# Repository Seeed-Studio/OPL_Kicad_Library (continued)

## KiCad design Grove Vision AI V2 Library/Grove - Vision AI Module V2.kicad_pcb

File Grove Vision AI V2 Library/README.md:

# Grove Vision AI V2 Library

This is the library for Grove Vision AI V2 and its case.

## Highlights(Content of Tables)

- [**The case for Grove Vision AI V2 - Himax**](#jump7)
- [**Preparatory Work: KiCad Download and Library Download**](#jump1)
- [**How to add and use Seeed OPL Footprint Libraries(Grove Vision AI V2)**](#jump2)
- [**How to add and use Seeed OPL Symbol Libraries(Grove Vision AI V2)**](#jump3)
- [**Scale up Your Creation With Seeed Studio Fusion**](#jump4)
- [**Co-Create with Seeed Studio**](#jump5)
- [**Resoureces**](#jump6)

## <span id="jump7">The case for Grove Vision AI V2 - Himax</span>

You can find the case here as well.

## <span id="jump1">Preparatory Work: KiCad Download and Library Download </span>

1. You can refer to this [link](https://www.kicad.org/download/) to download the KiCad software.

2. You can [download](https://github.com/Seeed-Studio/OPL_Kicad_Library) the "OPL_KiCad_Library" or use command to clone:

```
git clone https://github.com/Seeed-Studio/OPL_Kicad_Library.git
```

## How to add and use Seeed OPL Footprint Libraries

### <span id="jump2"> Take Grove Vision AI V2 and XIAO footprint as an Example </span>

1. Open KiCad and refer to `File -> Open Project`.

2. Find the "Gorve Vision AI V2 Library" and open the project:

3. Double click the "Grove Vision AI V2" PCB file and you will see below:

4. Refer to the `Perferences -> Manage Footprint Libraries`

5. Here is the existed footprint libraries and you can click the button below:

6. Find the "Gorve Vision AI V2 Library" and open the folder that contains the boards footprint:

Now you have added the "XIAO footprint library"

7. You can click here to use the added library:

8. Search for "seeed" and you can check the footprint added:

9. Click "ok" and you can add the XIAO RP2040 footprint into the "Grove Vision VI V2".

10. You can change any component on the Grove Vision VI V2 module and make it your own project.

## <span id="jump3"> How to add and use Seeed OPL Symbol Libraries </span>

### Take Grove Vision AI V2 and Sensor-Transducer as an Example:

1. Open KiCad and refer to `File -> Open Project`.

2. Find the "Gorve Vision AI V2 Library" and open the project:

3. Double click the "Grove Vision AI V2" .sch file and you will see below:

4. Refer to the `Perferences -> Manage Symbol Libraries`

5. Here is the existed symbol libraries and you can click the button below:

6. Find the "OPL_Sensor-Transducer" lib file:

Now you have added the "OPL_Sensor-Transducer library"

7. You can click here to use the added library:

8. Search for "OPL" and you can check the symbol added:

9. Click "ok" and you can add it into the "Grove Vision VI V2".

10. You can change any component on the Grove Vision VI V2 module and make it your own project.

## <span id="jump4"> Scale up Your Creation With Seeed Studio Fusion </span>

Seeed Studio Fusion serves as the comprehensive service platform for Seeed Studio, a global one-stop online platform offering PCB manufacturing, PCB assembly and hardware customization with global sourcing capability. Whether you need prototyping, mass production, custom solutions for open-source products, or the transformation of your creative ideas into profitable products, Seeed Studio Fusion can meet your requirements.

- [PCB/PCBA Design](https://www.seeedstudio.com/fusion_pcb.html)
- [Fusion Website](https://www.seeedstudio.com/fusion.html)
- **Email Contact**: fusion@seeed.io

## <span id="jump5"> Co-Create with Seeed Studio </span>

Leverage our Co-Create Program to transform your advanced prototype into a commercially successful product! This program is designed to optimize your product's journey from prototype to market by handling marketing, packaging, and distribution, allowing you to concentrate on refining your product. Upon acceptance of your prototype by Seeed, it will be showcased on the Seeed Studio marketplace. You'll receive a portion of the profits for each unit sold.

- [Application Form](https://docs.google.com/forms/d/e/1FAIpQLSe3A7_rIbn2OLO4JyJd_poGZodItCaRy6M6-3FtdqL3xG1Usg/viewform)
- [Co-Create Website](https://www.seeedstudio.com/co-create.html)

## <span id="jump6"> Resources </span>

- [Seeed Studio Open Parts List](https://files.seeedstudio.com/wiki/OPL/OPL_list.xlsx)

<!-- ## Even More Components!

As of last December, the [OPL has expanded](http://www.seeedstudio.com/blog/2018/12/04/just-what-you-wanted-for-xmas-introducing-the-new-shenzhen-open-parts-library-with-over-10000-parts/) from 800 components to more than 10,000 with the introduction of the new Shenzhen OPL. The original Seeed OPL is a catalog of components from Seeed’s own inventory, we have the parts and, we have been using them in our own production processes for years. The Shenzhen OPL contains parts from Shenzhen’s biggest components distributor that Seeed can quickly order for turnkey PCBA. While the sources are different, both can be used together with the Seeed Fusion PCBA service and reduce the production time to 7 days.

But with all the new components and many more to come, we don’t have enough resources to create the footprints for all of them. So, we are asking for help from you and the wider community to gradually build-up the library with us. As more and more users utilize the OPL and update the component libraries, the better the library will become for everyone. 

To assist with the process, we have designated a team of engineers to maintain the library and GitHub repositories. They will also help draw some footprints and connect schematic symbols. But while our engineers do their best to check each footprint, with the sheer number of components, it is inevitable that some errors will be present. It is unavoidable. So to make up for it, Seeed Fusion has introduced a re-manufacture promise: If an error in the library requires the boards to be re-manufactured, then we will re-manufacture the corrected boards for you for free. By using this library, you accept this potential risk.

## Footprint Design Guidelines
It is still early days, and we have a lot of catching up to do. So, the most important additions at this stage are unique symbols and footprints and any generic footprints that are missing. Part-specific symbols that use generic footprints and slight variations of generic footprints can be added later.

For consistency and ease of use, we would greatly appreciate it if everyone followed the same guidelines for new additions to the library:

-	The previous component libraries have been re-organized to match the Shenzhen OPL’s categorization. Please add new entries to the relevant sub-library according to the online OPL library’s classification.
-	Please take the time to study [KiCad’s own Library Convention](http://kicad-pcb.org/libraries/klc/) and ensure that the new footprints comply. Please refer to other footprints in the OPL or KiCad’s built-in footprints for reference. 
-	For MPN specific footprints, please follow the existing footprint naming convention for the footprint and name the corresponding schematic symbol with the manufacturer part number.

### Notes:
- #### The current version of the KiCad Library has been completely revamped in response to all the feedback we have recieved. Originally a direct import of the Eagle library, the old library did not comply with KiCad guidelines and placed features on the wrong layers. For the latest version, we have throroughly investigated the issues and revised (nearly) all of the footprints. Let us know if you think we missed something!

-	The Seeed OPL component libraries have been updated to match the Shenzhen OPL categories to aid in merging the two libraries. Some components will have moved to new homes, but this has not been updated on the website OPL library yet. We will update this soon!
-	Some of the original Seeed OPL KiCad component footprints have not been updated to match KiCad’s design guidelines yet. They are safe to use, and the pads are correct, but they may look a little ugly.
-	Unlike previous versions, we have uploaded the files individually as opposed to a whole zip file. We hope this will help you follow standard GitHub workflow to contribute changes. (Thanks for your feedback!)

There is a lot to consider in managing a large library like this, so we would greatly appreciate any ideas and feedback regarding how we can make the library more user-friendly. We’ll be monitoring the discussion section and the designated OPL section in our forums. You are also welcome to let us know by [e-mail](mailto:fusion@seeed.cc).

We hope the new maintained library will prove to be an invaluable resource to all of our PCBA users and beyond.

## Resources
1. A KiCad Bill-of-Materials (BOM) plugin to follow SeeedStudio's Fusion PCBA assembly service's template, This plugin is set up to use the KiCad schematic's part data as it is provided in Seeed Studio's Open Parts Library (OPL) collection for KiCad. - https://github.com/imrehg/kicad-bom-seeedstudio

 -->

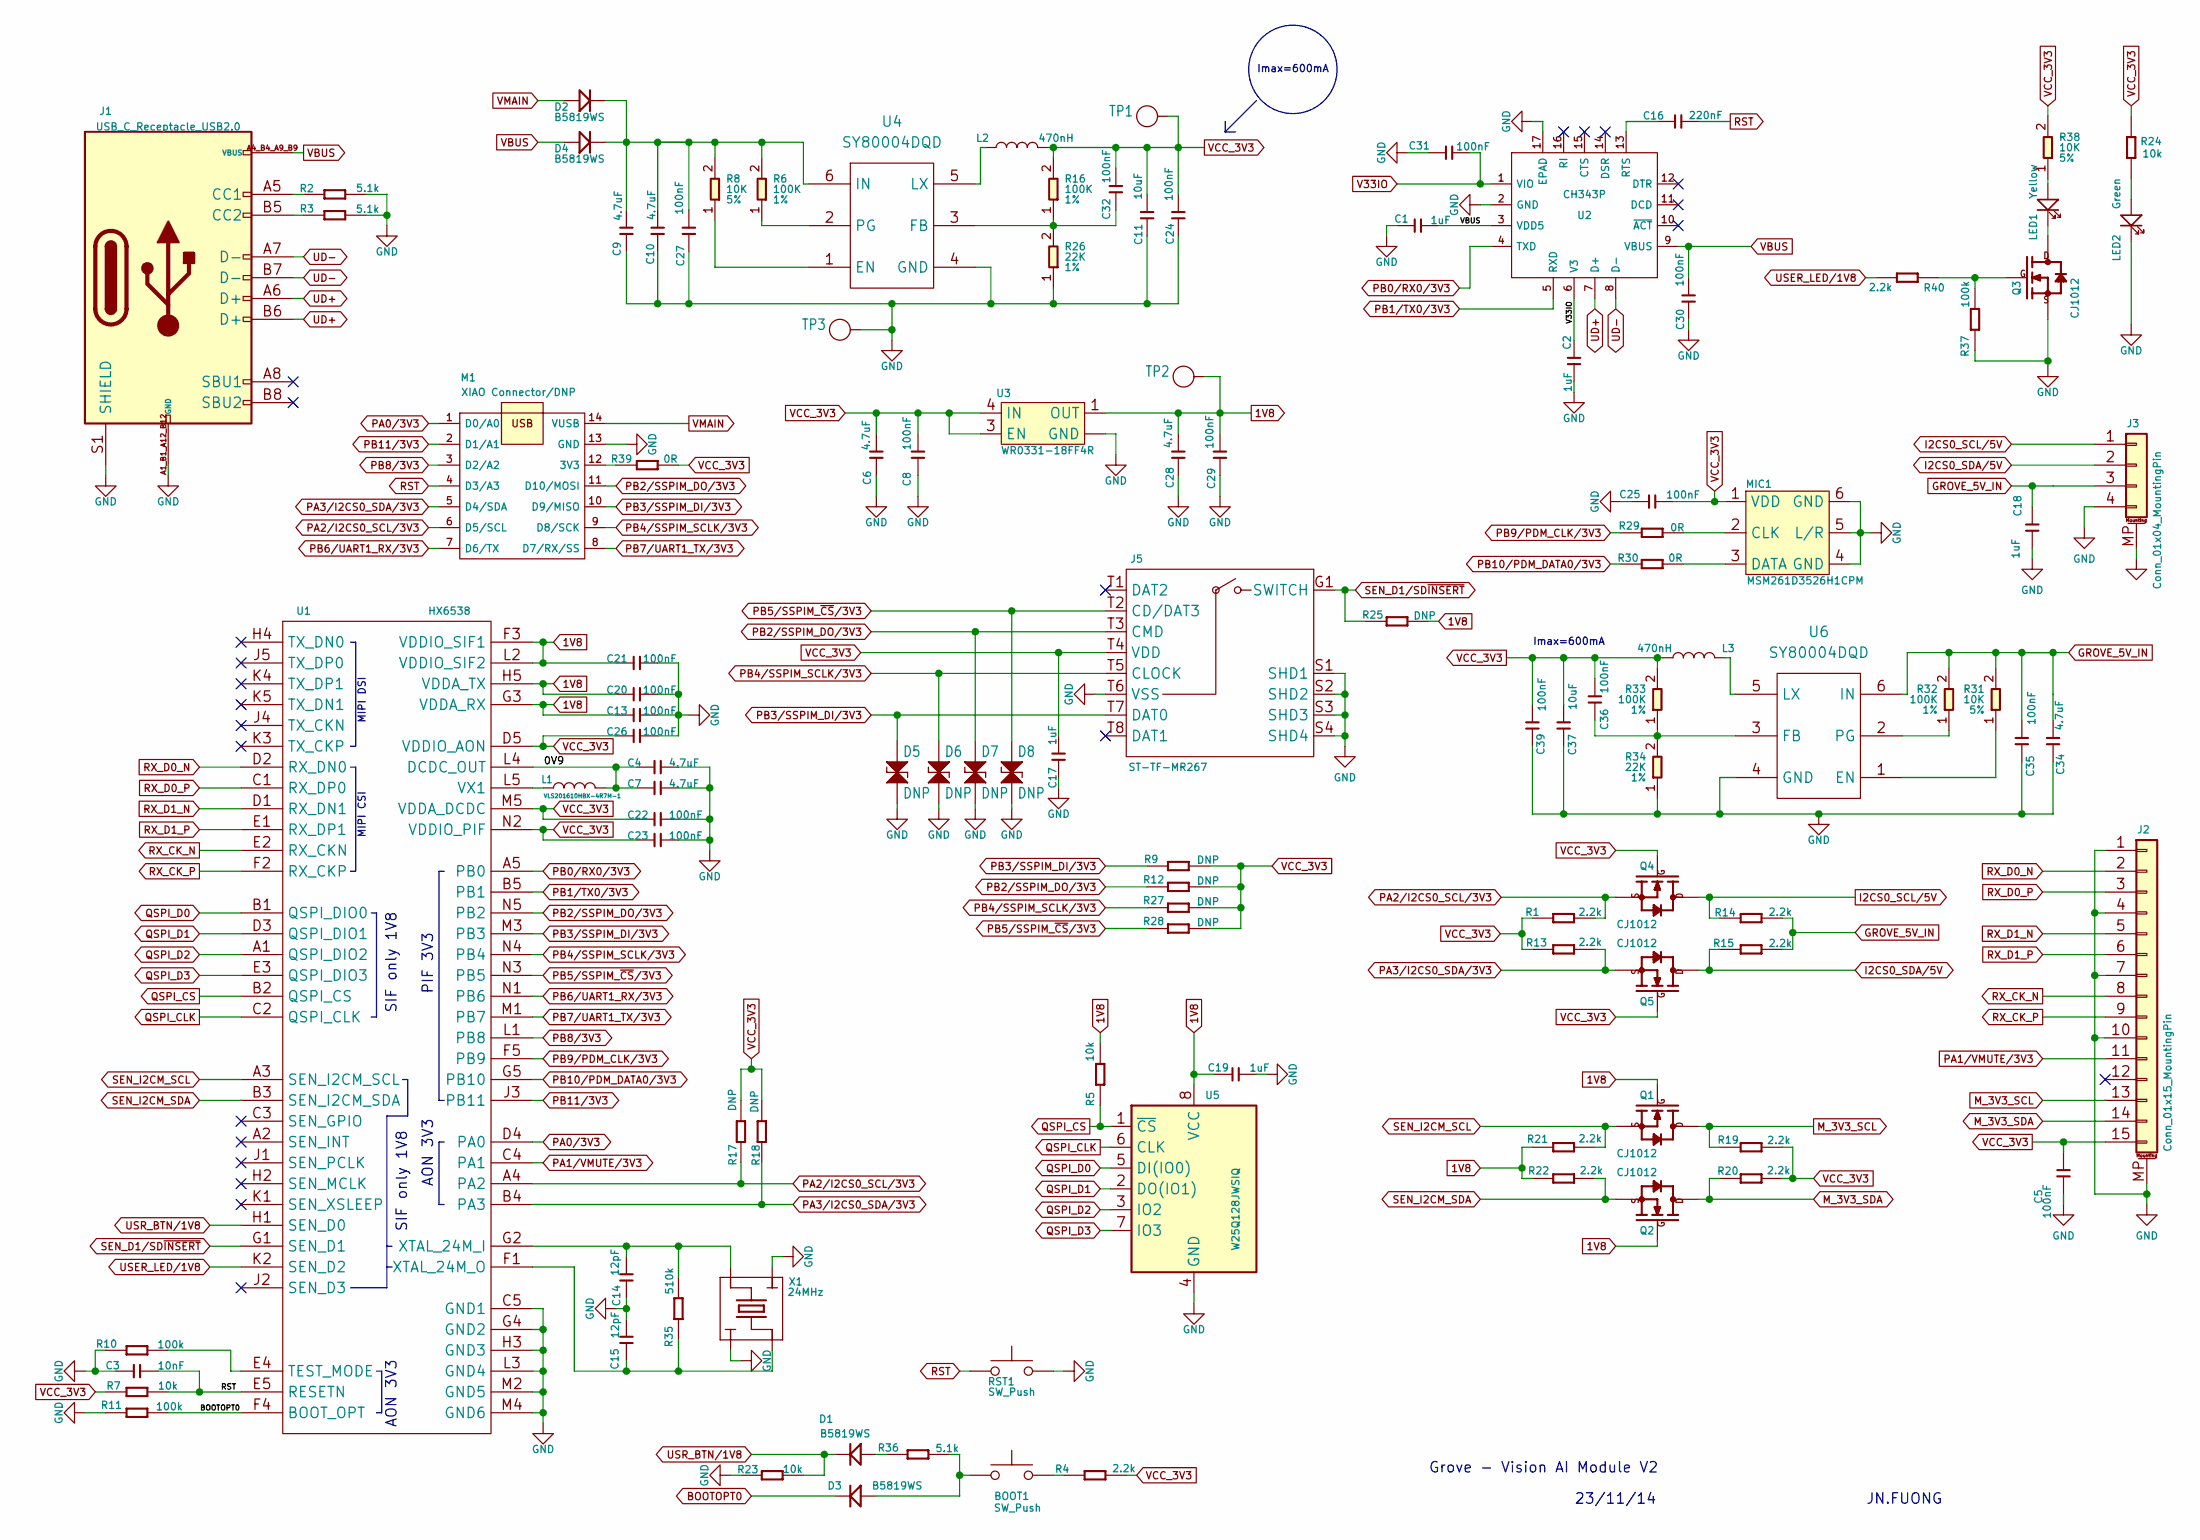
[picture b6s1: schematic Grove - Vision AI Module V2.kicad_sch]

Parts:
BOOT1: SW_Push; SW_Push_1P1T_NO_Vertical_Wuerth_434133025816
C1, C2, C17, C18, C19: 1uF; C0402
C3: 10nF; C0402
C4, C6, C7, C9, C10, C28, C34: 4.7uF; C0402
C5, C8, C13, C20, C21, C22, C23, C24, C25, C26, C27, C29, C30, C31, C32, C35, C36, C39: 100nF; C0402
C11, C37: 10uF; C0402
C14, C15: 12pF; C0402
C16: 220nF; C0402
D1, D2, D3, D4: B5819WS; D0805_SOD323
D5, D6, D7, D8: DNP; R0402; MPN DF2S6.8FS
J1: USB_C_Receptacle_USB2.0; USB2.0-TYPE-C
J2: Conn_01x15_MountingPin; FPC_DNC_15P_1.0mm
J3: Conn_01x04_MountingPin; 4P-SMD-2.0mm-RIGHT
J5: ST-TF-MR267; SD-TF-MR267; MPN SD-TF-MR267
L1: VLS201610HBX-4R7M-1; L0806
L2, L3: 470nH; L0603
LED1: Yellow; LED0402
LED2: Green; LED0402
M1: XIAO Connector/DNP; XIAO_Socket
MIC1: MSM261D3526H1CPM; MIC6P-3.5X2.65X0.94MM
Q1, Q2, Q3, Q4, Q5: CJ1012; SOT523
R1, R4, R13, R14, R15, R19, R20, R21, R22, R40: 2.2k; R0402
R2, R3, R36: 5.1k; R0402
R5, R7, R23, R24: 10k; R0402
R6, R16, R32, R33: 100K; R0402; Power Rating 1%; MPN RC0402JR-074K7L
R8, R31, R38: 10K; R0402; Power Rating 5%; MPN RC0402JR-074K7L
R9, R12, R17, R18, R25, R27, R28: DNP; R0402
R10, R11, R37: 100k; R0402
R26, R34: 22K; R0402; Power Rating 1%; MPN RC0402JR-074K7L
R29, R30, R39: 0R; R0402
R35: 510k; R0402
RST1: SW_Push; SW_Push_1P1T_NO_Vertical_Wuerth_434133025816
TP1, TP2, TP3: Test Point; TP-D35MIL; Part Type Test Point
U1: HX6538; WLCSP65_5.6x2.3x0.56mm
U2: CH343P; QFN-16-EP_3x3mm_P0.5mm_EP1x1mm
U3: WR0331-18FF4R; X2SON-4
U4, U6: SY80004DQD; DFN6-0.5-1.5X1.5X0.65MM; MPN SY80004DQD
U5: W25Q128JWSIQ; SOIC-8_5.23x5.23mm_P1.27mm
X1: 24MHz; 4P2016

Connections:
1V8: C13.1, C19.2, C20.1, C21.1, C28.1, C29.2, Q1.1 (G), Q2.1 (G), R5.1, R21.2, R22.2, R25.1, TP2.1 (T), U1.F3 (VDDIO_SIF1), U1.G3 (VDDA_RX), U1.H5 (VDDA_TX), U1.L2 (VDDIO_SIF2), U3.1 (OUT), U5.8 (VCC)
/0V9: C4.1, C7.1, L1.2, U1.L4 (DCDC_OUT)
BOOTOPT0: D3.1 (K), R11.1, U1.F4 (BOOT_OPT)
GND: C1.2, C2.2, C3.2, C4.2, C5.2, C6.2, C7.2, C8.1, C9.2, C10.2, C11.1, C13.2, C14.2, C15.1, C17.2, C18.2, C19.1, C20.2, C21.2, C22.2, C23.2, C24.1, C25.1, C26.2, C27.1, C28.2, C29.1, C30.1, C31.2, C34.2, C35.1, C37.1, C39.1, D5.1, D6.1, D7.1, D8.1, J1.A1_B1_A12_B12 (GND), J1.S1 (SHIELD), J2.1, J2.4, J2.7, J2.10, J2.MP (MountPin), J3.4, J3.MP (MountPin), J5.S1 (SHD1), J5.S2 (SHD2), J5.S3 (SHD3), J5.S4 (SHD4), J5.T6 (VSS), LED2.1 (K), M1.13 (GND), MIC1.4 (GND), MIC1.5 (L/R), MIC1.6 (GND), Q3.2 (S), R2.2, R3.2, R10.2, R11.2, R23.2, R26.1, R34.1, R37.2, RST1.2, TP3.1 (T), U1.C5 (GND1), U1.G4 (GND2), U1.H3 (GND3), U1.L3 (GND4), U1.M2 (GND5), U1.M4 (GND6), U2.2 (GND), U2.17 (EPAD), U3.2 (GND), U3.T (GND), U4.4 (GND), U5.4 (GND), U6.4 (GND), X1.2 (1), X1.4 (3)
GROVE_5V_IN: C18.1, C34.1, C35.2, J3.3, R14.1, R15.1, R31.2, R32.2, U6.6 (IN)
I2CS0_SCL/5V: J3.1, Q4.3 (D), R14.2
I2CS0_SDA/5V: J3.2, Q5.3 (D), R15.2
M_3V3_SCL: J2.13, Q1.3 (D), R19.2
M_3V3_SDA: J2.14, Q2.3 (D), R20.2
unnamed: BOOT1.2, R4.2
unnamed: D1.2 (A), R36.2
unnamed: C9.1, C10.1, C27.2, D2.1 (K), D4.1 (K), R6.2, R8.2, U4.6 (IN)
unnamed: BOOT1.1, D3.2 (A), R36.1
unnamed: J1.A5 (CC1), R2.1
unnamed: J1.B5 (CC2), R3.1
unnamed: LED1.2 (A), R38.1
unnamed: LED1.1 (K), Q3.3 (D)
unnamed: LED2.2 (A), R24.2
unnamed: M1.12 (3V3), R39.2
unnamed: MIC1.2 (CLK), R29.1
unnamed: MIC1.3 (DATA), R30.1
unnamed: Q3.1 (G), R37.1, R40.2
unnamed: R10.1, U1.E4 (TEST_MODE)
unnamed: L1.1, U1.L5 (VX1)
unnamed: C14.1, R35.1, U1.G2 (XTAL_24M_I), X1.3 (4)
unnamed: C15.2, R35.2, U1.F1 (XTAL_24M_O), X1.1 (2)
unnamed: C16.2, U2.13 (RTS)
unnamed: R8.1, U4.1 (EN)
unnamed: C32.1, R16.1, R26.2, U4.3 (FB)
unnamed: L2.1, U4.5 (LX)
unnamed: R6.1, U4.2 (PG)
unnamed: R31.1, U6.1 (EN)
unnamed: C36.1, R33.1, R34.2, U6.3 (FB)
unnamed: L3.1, U6.5 (LX)
unnamed: R32.1, U6.2 (PG)
PA0/3V3: M1.1 (D0/A0), U1.D4 (PA0)
PA1/VMUTE/3V3: J2.11, U1.C4 (PA1)
PA2/I2CS0_SCL/3V3: M1.6 (D5/SCL), Q4.2 (S), R1.1, R17.2, U1.A4 (PA2)
PA3/I2CS0_SDA/3V3: M1.5 (D4/SDA), Q5.2 (S), R13.1, R18.2, U1.B4 (PA3)
PB0/RX0/3V3: U1.A5 (PB0), U2.4 (TXD)
PB1/TX0/3V3: U1.B5 (PB1), U2.5 (RXD)
PB2/SSPIM_DO/3V3: D7.2, J5.T3 (CMD), M1.11 (D10/MOSI), R12.2, U1.N5 (PB2)
PB3/SSPIM_DI/3V3: D5.2, J5.T7 (DAT0), M1.10 (D9/MISO), R9.2, U1.M3 (PB3)
PB4/SSPIM_SCLK/3V3: D6.2, J5.T5 (CLOCK), M1.9 (D8/SCK), R27.2, U1.N4 (PB4)
PB5/SSPIM_~CS/3V3: D8.2, J5.T2 (CD/DAT3), R28.2, U1.N3 (PB5)
PB6/UART1_RX/3V3: M1.7 (D6/TX), U1.N1 (PB6)
PB7/UART1_TX/3V3: M1.8 (D7/RX/SS), U1.M1 (PB7)
PB8/3V3: M1.3 (D2/A2), U1.L1 (PB8)
PB9/PDM_CLK/3V3: R29.2, U1.F5 (PB9)
PB10/PDM_DATA0/3V3: R30.2, U1.G5 (PB10)
PB11/3V3: M1.2 (D1/A1), U1.J3 (PB11)
QSPI_CLK: U1.C2 (QSPI_CLK), U5.6 (CLK)
QSPI_CS: R5.2, U1.B2 (QSPI_CS), U5.1 (~CS)
QSPI_D0: U1.B1 (QSPI_DIO0), U5.5 (DI(IO0))
QSPI_D1: U1.D3 (QSPI_DIO1), U5.2 (DO(IO1))
QSPI_D2: U1.A1 (QSPI_DIO2), U5.3 (IO2)
QSPI_D3: U1.E3 (QSPI_DIO3), U5.7 (IO3)
RST: C3.1, C16.1, M1.4 (D3/A3), R7.1, RST1.1, U1.E5 (RESETN)
RX_CK_N: J2.8, U1.E2 (RX_CKN)
RX_CK_P: J2.9, U1.F2 (RX_CKP)
RX_D0_N: J2.2, U1.D2 (RX_DN0)
RX_D0_P: J2.3, U1.C1 (RX_DP0)
RX_D1_N: J2.5, U1.D1 (RX_DN1)
RX_D1_P: J2.6, U1.E1 (RX_DP1)
SEN_D1/SD~INSERT: J5.G1 (SWITCH), R25.2, U1.G1 (SEN_D1)
SEN_I2CM_SCL: Q1.2 (S), R21.1, U1.A3 (SEN_I2CM_SCL)
SEN_I2CM_SDA: Q2.2 (S), R22.1, U1.B3 (SEN_I2CM_SDA)
UD+: J1.A6 (D+), J1.B6 (D+), U2.7 (D+)
UD-: J1.A7 (D-), J1.B7 (D-), U2.8 (D-)
USER_LED/1V8: R40.1, U1.K2 (SEN_D2)
USR_BTN/1V8: D1.1 (K), R23.1, U1.H1 (SEN_D0)
V33IO: C2.1, C31.1, U2.1 (VIO), U2.6 (V3)
VBUS: C1.1, C30.2, D4.2 (A), J1.A4_B4_A9_B9 (VBUS), U2.3 (VDD5), U2.9 (VBUS)
VCC_3V3: C5.1, C6.1, C8.2, C11.2, C17.1, C22.1, C23.1, C24.2, C25.2, C26.1, C32.2, C36.2, C37.2, C39.2, J2.15, J5.T4 (VDD), L2.2, L3.2, MIC1.1 (VDD), Q4.1 (G), Q5.1 (G), R1.2, R4.1, R7.2, R9.1, R12.1, R13.2, R16.2, R17.1, R18.1, R19.1, R20.1, R24.1, R27.1, R28.1, R33.2, R38.2, R39.1, TP1.1 (T), U1.D5 (VDDIO_AON), U1.M5 (VDDA_DCDC), U1.N2 (VDDIO_PIF), U3.3 (EN), U3.4 (IN)
VMAIN: D2.2 (A), M1.14 (VUSB)

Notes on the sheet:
MIPI CSI
AON 3V3
MIPI DSI
PIF 3V3
SIF only 1V8
Imax=600mA
23/11/14
Grove - Vision AI Module V2
JN.FUONG

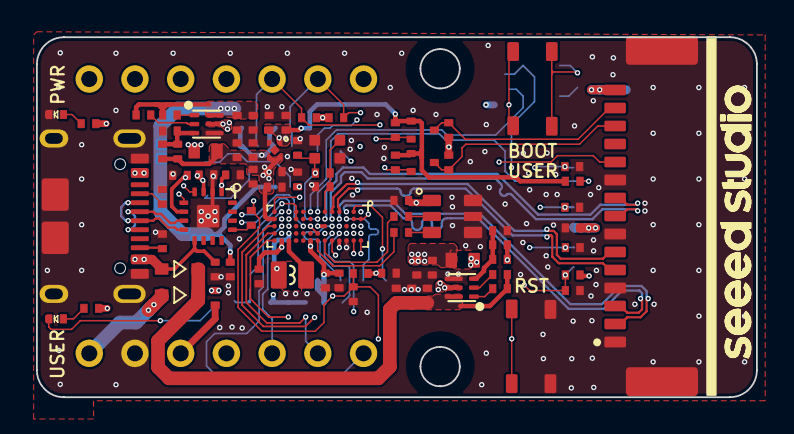
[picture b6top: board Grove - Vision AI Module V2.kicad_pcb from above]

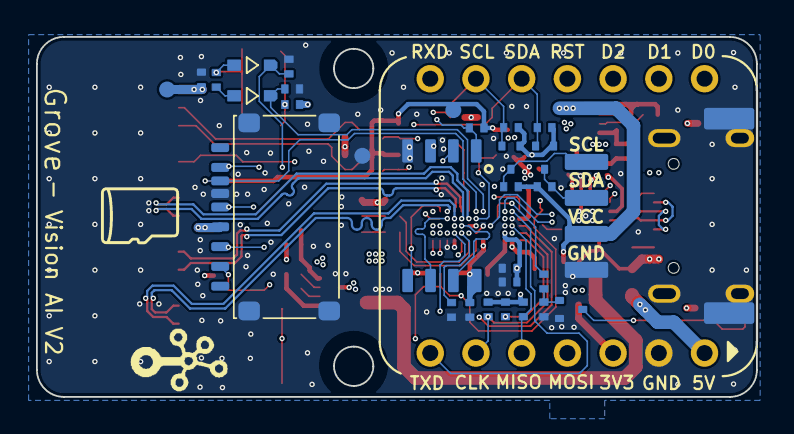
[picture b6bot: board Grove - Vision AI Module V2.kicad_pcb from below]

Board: 4 copper layers, 40.0 x 20.0 mm, 112 parts (31 on the bottom side), 75 nets.

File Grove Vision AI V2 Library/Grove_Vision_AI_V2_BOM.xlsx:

Layer Jump | Number | Name | Specification | Operating Temperature | MPN Code | Quantity | Base | Plug Position | Process
N | 301010000 | SMD RES 0R-5%-1/16W;0402 |  | -55°C to 155°C | RC0402JR-070RL | 3 | 1 | R29,R30,R39 | SMT1
N | 301010004 | SMD RES 10K-5%-1/16W;0402 |  | -55°C to 155°C | RC0402JR-0710KL | 7 | 1 | R5,R7,R8,R23,R24,R31,R38 | SMT1
N | 301010008 | SMD RES 510K-5%-1/16W;0402 |  | -55°C to 155°C | RC0402JR-07510KL | 1 | 1 | R35 | SMT1
N | 301010456 | SMD RES 100K-1%-1/16W;0402 |  | -55°C to 155°C | RC0402FR-07100KL | 7 | 1 | R6,R10,R11,R16,R32,R33,R37 | SMT1
N | 301010495 | SMD RES;5.1K-1%-1/16W;0402 |  | -55°C to 155°C | RC0402FR-075K1L | 3 | 1 | R2,R3,R36 | SMT1
N | 301010746 | SMD RES 2.2K-1%-1/16W;0402 |  | -55°C to 155°C | RC0402FR-072K2L | 10 | 1 | R1,R4,R13,R14,R15,R19,R20,R21,R22,R40 | SMT1
N | 301011331 | SMD RES 22.1K-1%-1/16W;0402 |  | -55°C to 155°C | RC0402FR-0722K1L | 2 | 1 | R26,R34 | SMT1
N | 302010004 | SMD CAP Ceramic 100nF-16V-10%-X7R;0402 |  | -55°C to 125°C | CC0402KRX7R7BB104 | 18 | 1 | C5,C8,C13,C20,C21,C22,C23,C24,C25,C26,C27,C29,C30,C31,C32,C35,C36,C39 | SMT1
N | 302010006 | SMD CAP Ceramic 10nF-50V-10%-X7R;0402 |  | -55°C to 125°C | CC0402KRX7R9BB103 | 1 | 1 | C3 | SMT1
N | 302010049 | SMD CAP Ceramic 12pF-50V-5%-NPO;0402 |  | -55°C to 125°C | CC0402JRNPO9BN120 | 2 | 1 | C14,C15 | SMT1
N | 302010051 | SMD CAP Ceramic 220nF-16V-10%-X7R;0402 |  | -55°C to 125°C | CC0402KRX7R7BB224 | 1 | 1 | C16 | SMT1
N | 302010407 | SMD CAP Ceramic 4.7uF-10V-10%-X5R;0402 |  | -55°C to 85°C | CC0402KRX5R6BB475 | 7 | 1 | C4,C6,C7,C9,C10,C28,C34 | SMT1
N | 302010519 | SMD CAP Ceramic 10uF-10V-20%-X5R;0402 |  | -55°C to 85°C | CC0402MRX5R6BB106 | 2 | 1 | C11,C37 | SMT1
N | 302013249 | SMD CAP Ceramic 1uF-10V-10%-X5R;0402 |  | -55°C to 85°C | CL05A105KP5NNNC | 5 | 1 | C1,C2,C17,C18,C19 | SMT1
N | 303010544 | SMD Inductor 4.7uH-20%-1.1A;0806 |  | -40°C to 105°C | VLS201610HBX-4R7M-1 | 1 | 1 | L1 | SMT1
N | 303011858 | SMD Inductor 470nH-20%-2.6A;0603 |  | -40°C to 125°C | TFM160808ALC-R47MTAA | 2 | 1 | L2,L3 | SMT1
N | 304011053 | SMD Diode Schottky 40V-1A;SOD-323 |  |  | B5819WS SL | 4 | 1 | D1,D2,D3,D4 | SMT1
N | 304090121 | SMD LED Clear-Green;0402 | As posted |  | BL-HGE37A-AV-TRB | 1 | 1 | LED2 | SMT1
N | 304090746 | SMD LED Clear-Yellow;0402 | As posted |  | 16-213/Y2C-AN2Q1B/3T | 1 | 1 | LED1 | SMT1
N | 305030071 | SMD MOSFET N-CH 20V-500mA;SOT-523 |  |  | CJ1012 | 5 | 1 | Q1,Q2,Q3,Q4,Q5 | SMT1
N | 306011444 | SMD Crystal;24MHz-12pF-10ppm-4P-2.0*1.6*0.5mm |  | -40°C to 85°C | Y2400FE001 | 1 | 1 | X1 | SMT1
N | 310011697 | SMD IC MCU;Dual Cortex-M55 Core(Max 400MHz)-With a 400MHz NPU;WLCSP-65 | L5.58*W2.27mm | -40°C to 85°C | HX6538-A01TWA | 1 | 1 | U1 | SMT1
N | 310032794 | SMD IC PMIC;DCDC Buck-ADJ-2.2MHz-4A;DFN1.5×1.5-6 |  | -40°C to 85°C | SY80004DQD | 2 | 1 | U4,U6 | SMT1
N | 310032813 | SMD IC PMIC;LDO-1.8V-300mA;XTDFN-1*1-4L |  | -40°C to 125°C | SGM2036S-1.8XXDH4G/TR | 1 | 1 | U3 | SMT1
N | 310071431 | SMD IC Interface USB to High Speed TTL;QFN16 | USB to High-Speed Serial Port | -40°C to 85°C | CH343P | 1 | 1 | U2 | SMT1
N | 310091468 | SMD IC Memory;128Mbit-1.8V;SOIC-8 |  | -40°C to 85°C | W25Q128JWSIQ | 1 | 1 | U5 | SMT1
N | 311020009 | SMD Top Button 4N;4P-L4.6*W3.2*H2.5mm |  | -20°C to 70°C | SKRPADE010 | 1 | 1 | RST1 | SMT1
N | 311020518 | SMD Top Button 1.57N;4P-L4.6*W3.2*H2.5mm |  | -30°C to 85°C | SKRPABE010 | 1 | 1 | BOOT1 | SMT1
N | 312030502 | SMD DIGITAL MIC OMNI -26dBFS;OCLGA-4:3.5*2.65*0.94mm |  | -40˚C to 100˚C | MSM261D3526H1CPM | 1 | 1 | MIC1 | SMT1
N | 319015667 | PCB;Grove - Vision AI Module V2 -蓝油白字-4层 | 20*40*1.6mm-ENIG-FR4;Steel mesh code；404012305 |  |  | 1 | 1 |  | SMT1
N | 320011358 | SMD USB TYPE C-W/P;12+4P-8.94*7.35*3.26mm |  | -30°C to 85°C | USB-31C-F-16P-L7.35 | 1 | 1 | J1 | SMT1
N | 320031231 | DIP Black Female Header VERT;1*7P-2.54-5.0mm |  | -40℃ to 105℃ |  | 2 | 1 | P8,P9 | Unit
N | 320060904 | SMD FPC CONN Bottom Contact;15P-1.0mm;L19.9*W6.76*H2.0mm |  | -30°C to 85°C | ST-FPC-W102015-D | 1 | 1 | J2 | SMT1
N | 320090535 | SMD uSD Card Holder;9+4P-L11.25*W6.96*H1.42mm |  | -25°C to 70°C | ST-TF-MR267 | 1 | 1 | J5 | SMT1
N | 320110032 | SMD Grove Female Header-Beige;4P-2.0-90D | 2.0-4PHorizontal Mount with Locking Socket |  | PHS-4A horizontal mount | 1 | 1 | J3 | SMT1

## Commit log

2017-12-01 Correct micro-USB connector footprint
    1. Corrected Micro-USB footprint drill hole from circular shape to oval xdim:0.5mm, ydim:1.2mm.
    2. This was following sample footprint recommendations from the FCI 10118193-0001LF datasheet.
    3. Without the modification there is a collision with the FCI model step file and the PCB drill hole.
    4. Additional checks will have to be done to assess if this is compatible with the Suntech connectors.
2018-11-27 Update the footprint of connectors and capacitors
2019-01-10 Create Seeed_Fusion_PCBA_OPL_Component_Library_for_KiCad\
2019-01-10 Create txt
2019-01-11 Updated OPL_Circuit_Protection
2019-02-14 Added OPL Excel spreadsheet
    This spreadsheet contains all the parts in the Seeed and Shenzhen OPL as of 2019-02-14. It also contains keyword translations for many parts in the Shenzhen OPL that are not currently updated in the 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
2019-05-03 added ceramic 2.2uF 0805 & 0603
2019-06-11 added SMD-CRYSTAL-8MHZ-18PF-10PPM-80R_HC49US_
2019-06-11 added CERAMIC-33PF-50V-5%-NPO_0402_
2019-06-11 CERAMIC-18PF-50V-5%-NPO_0402_
2019-06-11 added CERAMIC-12PF-50V-5%-NPO_0402_
2019-06-12 footprint filter for SMD-CRYSTAL-8MHZ-18PF-10PPM-80R_HC49S_
2019-06-12 added CERAMIC-20PF-50V-5%-NPO_0402_
2019-06-18 TANTALUM-SMD-10UF-10V-10%_AVX-A_ pins renamed (fixes #17)
    + -> 1
    - -> 2
2019-06-18 added CERAMIC-1UF-25V-10%-X7R_0603_
2019-08-10 ZX62B micro usb connector: Don't hide pin names in schematic
2020-05-14 Add URLs to datasheets
    Used the following python script to add URLs to all library components:
    import re
    import argparse
    import io
    argparser = argparse.ArgumentParser()
    argparser.add_argument("files", nargs='+')
2024-01-22 Add: Grove Vision AI V2 Kicad
2024-01-24 Update: update contents
2024-01-24 Add: Add Grove Vision AI V2 BOM file
2024-01-26 Add: add required files
2024-03-08 Add: add wio series files
2024-03-23 Add: Add XIAO nRF52840 symbol to `Seeed_Studio_XIAO_Series.kicad_sym`.
    Could not confirm from pinout diagram which NFC pad is NFC1/NFC2 but should not impact usage for NFC antenna.
2024-05-29 Update: update Grove modules KiCAD libraries
2024-10-08 Add sync_issues GitHub Action for workflows
2024-10-14 Update: update XIAO series footprint
2024-10-15 Add: Add wio-sx1262 module
2024-11-25 Fix: XIAO Name
2024-12-29 Minor spelling corrections for README.md
2025-01-08 ci: add an action to automatically close stale issues and PRs
2025-09-05 Update wio LR1121 files
2025-09-08 Add KiCAD files
2025-09-23 Add the XIAO Family KiCAD
2025-09-23 Add XIAO Family KiCAD
2025-09-24 Update: update XIAO family and related files
2025-09-25 Update XIAO Series family images and files
2025-11-24 Add Creative Commons License
    Added the Creative Commons Attribution-ShareAlike 4.0 International Public License to the project.
2025-12-29 Fix XIAO ESP32C6 symbol Value property
2026-03-18 Add new KiCad footprints for XIAO series variants
2026-04-17 Update the footprint and symbol files for the XIAO ESP32-S3 Plus
2026-04-17 Update the footprint and symbol files for the XIAO ESP32-S3 Plus (#37)
2026-05-17 Remap battery pins in esp32c6 library
    The symbol and footprints had different pin numbers, this changes the symbol to match BAT+ for pin 24 and BAT- for pin 23 (instead of 33 and 34, which did not have corresponding pads)
2026-05-18 Fix pins in Seeed_Studio_XIAO_Series.kicad_sym
2026-06-23 add:xiao series library
2026-06-23 fix:The original file is incorrect
2026-06-23 add:xiao series library (#39)
    * add:xiao series library
    * fix:The original file is incorrect
